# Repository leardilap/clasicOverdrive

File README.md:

# 3D view

# Order Online

https://aisler.net/p/NZXUXPBU

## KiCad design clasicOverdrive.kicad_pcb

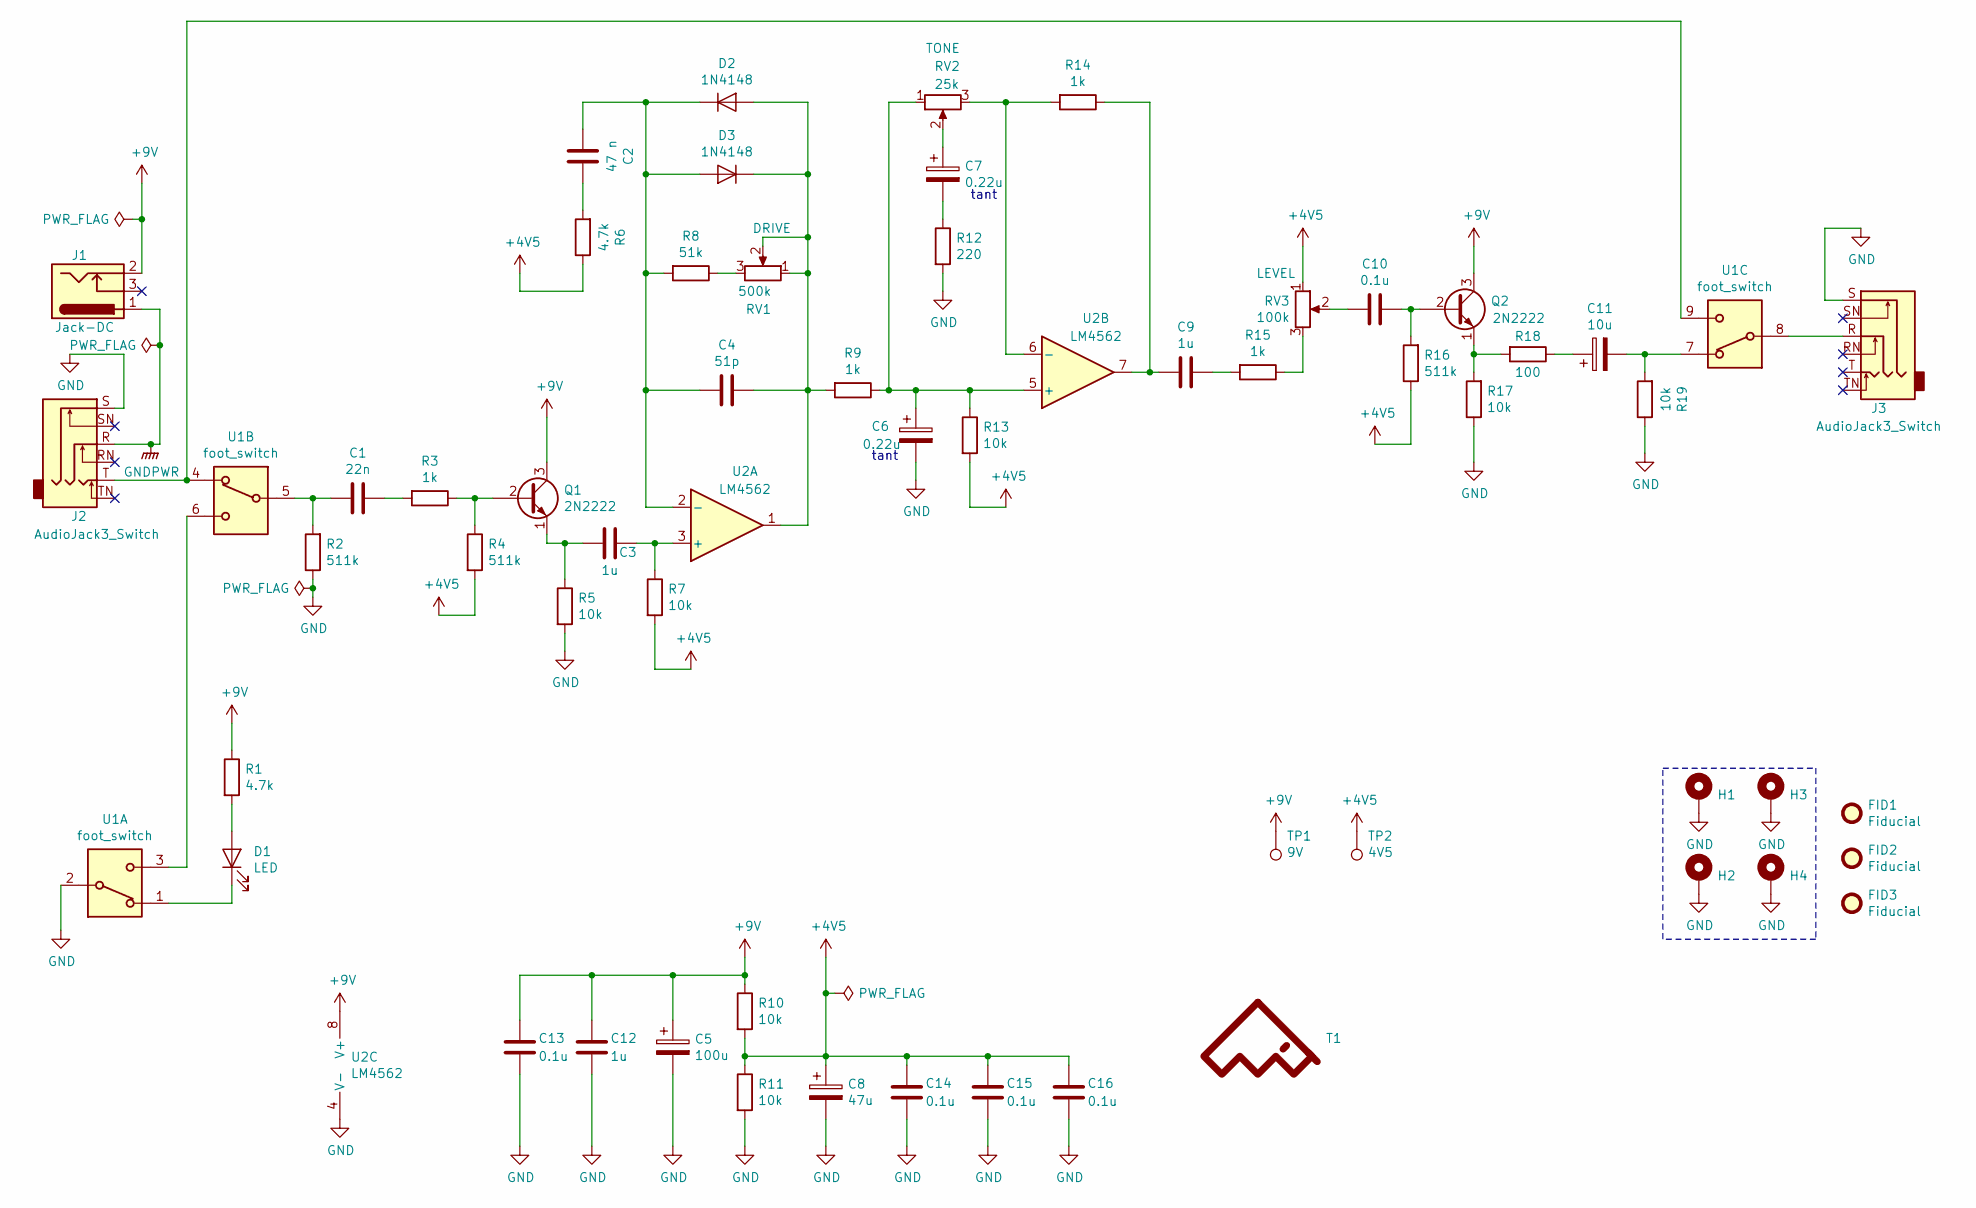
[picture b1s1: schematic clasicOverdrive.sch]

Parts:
C1: 22n; C_0805_2012Metric; Digi-Key 399-1163-1-ND
C2: 47 n; C_0805_2012Metric; Digi-Key 1276-2527-1-ND
C3, C9, C12: 1u; C_0805_2012Metric; Digi-Key 1276-6471-1-ND
C4: 51p; C_0805_2012Metric; Digi-Key 1276-2670-1-ND
C5: 100u; CP_EIA-6032-28_Kemet-C; Digi-Key 399-11392-1-ND
C6, C7: 0.22u; CP_EIA-2012-12_Kemet-R; Digi-Key 718-2502-1-ND
C8: 47u; CP_EIA-3216-18_Kemet-A; Digi-Key 718-2387-1-ND
C10, C13, C14, C15, C16: 0.1u; C_0805_2012Metric; Digi-Key 399-8000-1-ND
C11: 10u; C_1206_3216Metric; Digi-Key 478-10743-1-ND
D1: LED; LED_1206_3216Metric; Digi-Key 732-4989-1-ND
D2, D3: 1N4148; D_SOD-323_HandSoldering; Digi-Key 1N4148WXTPMSCT-ND
FID1, FID2, FID3: Fiducial; Fiducial_1mm_Mask2mm
H1, H2, H3, H4: MountingHole_Pad; MountingHole_2.7mm_M2.5_Pad_Via
J1: Jack-DC; BarrelJack_Horizontal; Digi-Key CP-002A-ND
J2, J3: AudioJack3_Switch; Jack_6.35mm_Amphenol_ACJS-MHOM; Digi-Key 889-1818-ND
Q1, Q2: 2N2222; TO-18-3; Digi-Key 1514-2N2222APBFREE-ND
R1, R6: 4.7k; R_0603_1608Metric; Digi-Key 311-4.70KHRCT-ND
R2, R4, R16: 511k; R_0603_1608Metric; Digi-Key 311-511KHRCT-ND
R3, R9, R14, R15: 1k; R_0603_1608Metric; Digi-Key 311-1.00KHRCT-ND
R5, R7, R10, R11, R13, R17, R19: 10k; R_0603_1608Metric; Digi-Key 311-10.0KHRCT-ND
R8: 51k; R_0603_1608Metric; Digi-Key YAG3616CT-ND
R12: 220; R_0603_1608Metric; Digi-Key 311-220HRCT-ND
R18: 100; R_0603_1608Metric; Digi-Key 311-100HRCT-ND
RV1: 500k; Potentiometer_Bourns_PTV09A-1_Single_Vertical; Digi-Key PTV09A-4020F-A504-ND
RV2: 25k; Potentiometer_Bourns_PTV09A-1_Single_Vertical; Digi-Key PTV09A-4020F-B203-ND
RV3: 100k; Potentiometer_Bourns_PTV09A-1_Single_Vertical; Digi-Key PTV09A-4020F-B104-ND
T1: LA_LOGO; LA_LOGO_MASK
TP1: 9V; TestPoint_Pad_D1.5mm
TP2: 4V5; TestPoint_Pad_D1.5mm
U1: foot_switch; Foot_Switch_E-Switch_FS57003PLT2B2M2QE; Digi-Key EG5492-ND
U2: LM4562; SOIC-8_3.9x4.9mm_P1.27mm; Digi-Key 296-35279-1-ND

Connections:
+4V5: C8.1, C14.1, C15.1, C16.1, R4.2, R6.1, R7.2, R10.2, R11.1, R13.2, R16.1, RV3.1, TP2.1
+9V: C5.1, C12.1, C13.1, J1.2, Q1.3 (C), Q2.3 (C), R1.1, R10.1, TP1.1, U2.8 (V+)
GND: C5.2, C6.2, C8.2, C12.2, C13.2, C14.2, C15.2, C16.2, H1.1, H2.1, H3.1, H4.1, J2.S, J3.S, R2.1, R5.2, R11.2, R12.2, R17.1, R19.1, U1.2, U2.4 (V-)
GNDPWR: J1.1, J2.R
unnamed: C1.1, R3.2
unnamed: C1.2, R2.2, U1.5
unnamed: C2.1, R6.2
unnamed: C2.2, C4.1, D2.1 (K), D3.2 (A), R8.2, U2.2 (-)
unnamed: C3.1, R7.1, U2.3 (+)
unnamed: C3.2, Q1.1 (E), R5.1
unnamed: C4.2, D2.2 (A), D3.1 (K), R9.2, RV1.1, RV1.2, U2.1
unnamed: C6.1, R9.1, R13.1, RV2.1, U2.5 (+)
unnamed: C7.1, RV2.2
unnamed: C7.2, R12.1
unnamed: C9.1, R15.2
unnamed: C9.2, R14.1, U2.7
unnamed: C10.1, Q2.2 (B), R16.2
unnamed: C10.2, RV3.2
unnamed: C11.1, R18.1
unnamed: C11.2, R19.2, U1.7
unnamed: D1.1 (K), U1.1
unnamed: D1.2 (A), R1.2
unnamed: J2.T, U1.4, U1.9
unnamed: J3.R, U1.8
unnamed: Q1.2 (B), R3.1, R4.1
unnamed: Q2.1 (E), R17.2, R18.2
unnamed: R8.1, RV1.3
unnamed: R14.2, RV2.3, U2.6 (-)
unnamed: R15.1, RV3.3
unnamed: U1.3, U1.6

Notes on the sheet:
tant

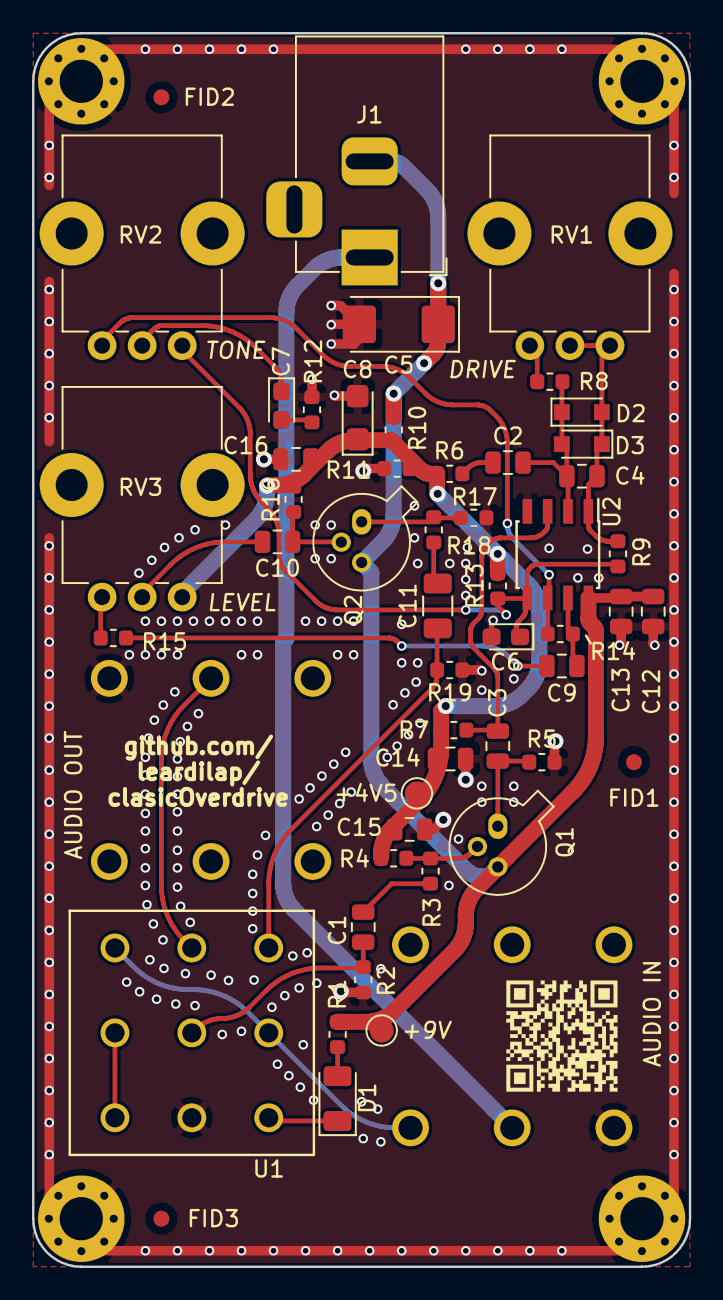
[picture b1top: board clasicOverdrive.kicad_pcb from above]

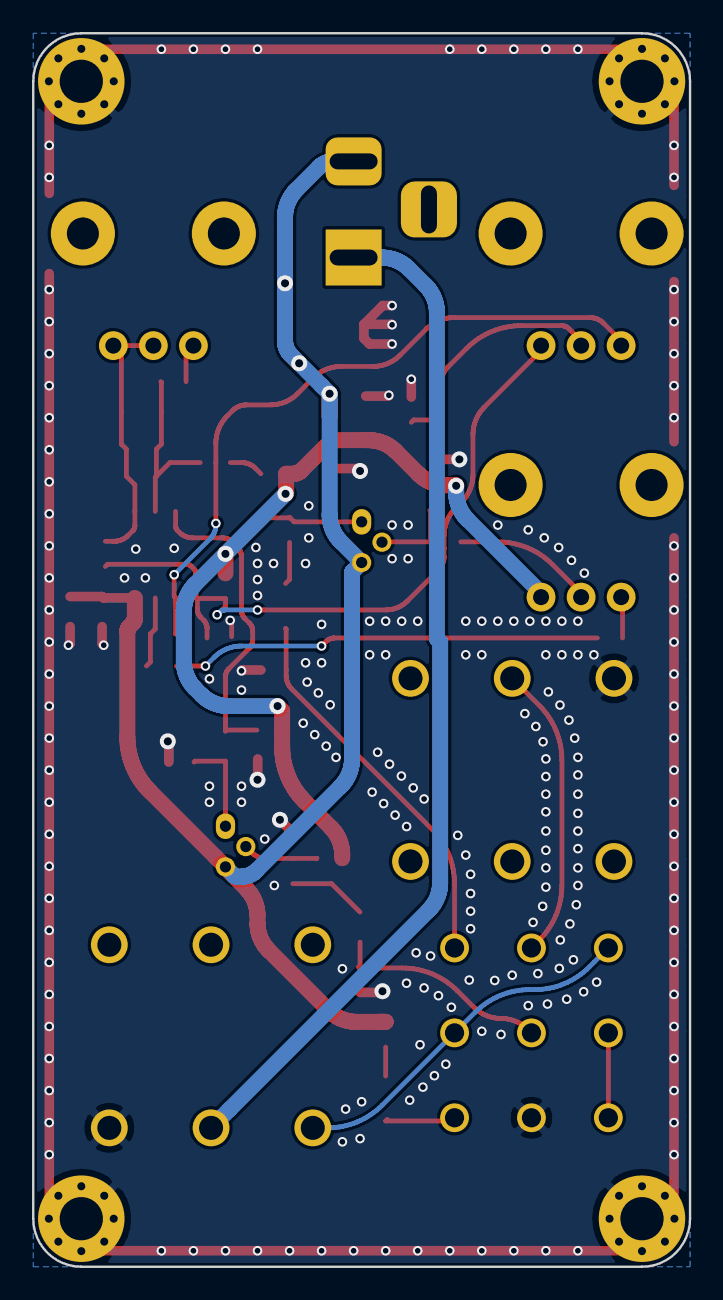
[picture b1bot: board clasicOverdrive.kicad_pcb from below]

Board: 2 copper layers, 41.0 x 77.0 mm, 58 parts (2 on the bottom side), 30 nets.

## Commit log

2018-04-11 schematic finished
2018-04-11 annotate and footprint assignment init
2018-04-12 all footprints added and layout of pcb complete
2018-04-15 after freeRouter run
2018-04-21 Board Finished
2018-08-08 updated bom and footprint for the diodes@
2018-11-07 update pcb and schematic with pads
2019-01-17 3D updated of transistors
2019-11-30 Rev A
2019-11-30 cache of footprints
2019-11-30 Gerbers Rev A
2019-11-30 Rev A fix silkscreen and test points names
2019-11-30 Rev A: include mask of bottom
2019-12-01 Rev A: Submitted
2019-12-01 Rev-A Fabricated 2019_12_01
2019-12-01 updated pdf
2019-12-09 Rev A - fabrication 2: silkscreen QR and website
